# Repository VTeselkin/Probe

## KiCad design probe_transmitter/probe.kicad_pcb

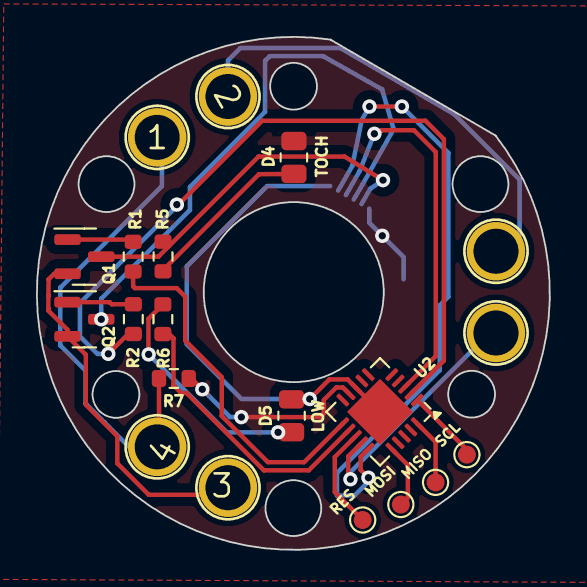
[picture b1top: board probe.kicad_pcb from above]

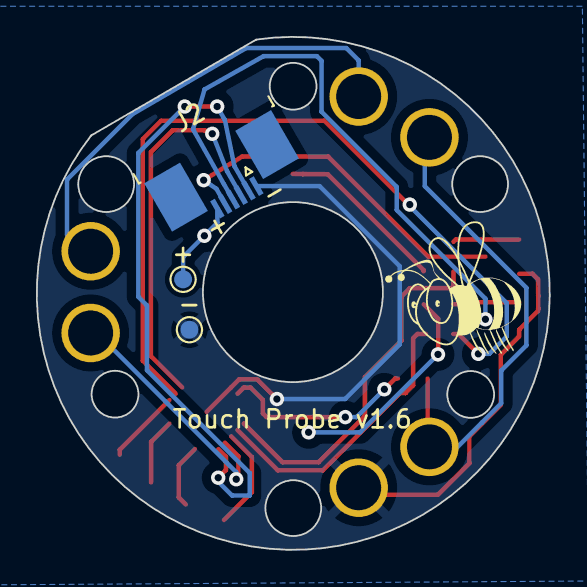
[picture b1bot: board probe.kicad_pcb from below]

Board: 2 copper layers, 28.5 x 28.5 mm, 22 parts (4 on the bottom side), 18 nets.

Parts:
1, 2, 3, 4: (no value)
 : Touch Probe v1.6; LOGO
+: PB0; TestPoint_Pad_D1.0mm
-: PB0; TestPoint_Pad_D1.0mm
D4, D5: LED; R_0805_2012Metric
J2: Conn_01x06; TE_0-1734839-6_1x06-1MP_P0.5mm_Horizontal
MISO: PB1; TestPoint_Pad_D1.0mm
MOSI: PB0; TestPoint_Pad_D1.0mm
Q1, Q2: PMST2222; SOT-23
R1: R1K; R_0603_1608Metric
R2: R1k; R_0603_1608Metric
R5, R6: R39; R_0603_1608Metric
R7: R10M; R_0603_1608Metric
RES: PB5; TestPoint_Pad_D1.0mm
SCL: PB2; TestPoint_Pad_D1.0mm
U2: ATtiny84-20M; QFN-20-1EP_4x4mm_P0.5mm_EP2.6x2.6mm

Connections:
+3.3V: +.1, D4.2 (A), J2.6, R7.2, U2.9 (VCC)
/PAD1: 1.1, 2.1, 4.1, R7.1, U2.14 (PB2)
GND: 3.1, -.1, D5.1 (K), J2.1, Q1.2 (E), Q2.2 (E), U2.8 (GND), U2.21 (GND)
unnamed: D4.1 (K), R5.2
unnamed: D5.2 (A), R6.2
unnamed: J2.2, U2.15 (PA7)
unnamed: J2.3, U2.3 (PA2)
unnamed: J2.4, Q2.3 (C)
unnamed: J2.5, Q1.3 (C), R5.1
unnamed: Q1.1 (B), R1.2
unnamed: Q2.1 (B), R2.2
unnamed: R2.1, U2.2 (PA3)
unnamed: SCL.1, U2.1 (PA4)
unnamed: MISO.1, U2.20 (PA5)
unnamed: MOSI.1, U2.16 (PA6)
unnamed: R1.1, U2.11 (XTAL1/PB0)
unnamed: R6.1, U2.12 (XTAL2/PB1)
unnamed: RES.1, U2.13 (~RESET/PB3)

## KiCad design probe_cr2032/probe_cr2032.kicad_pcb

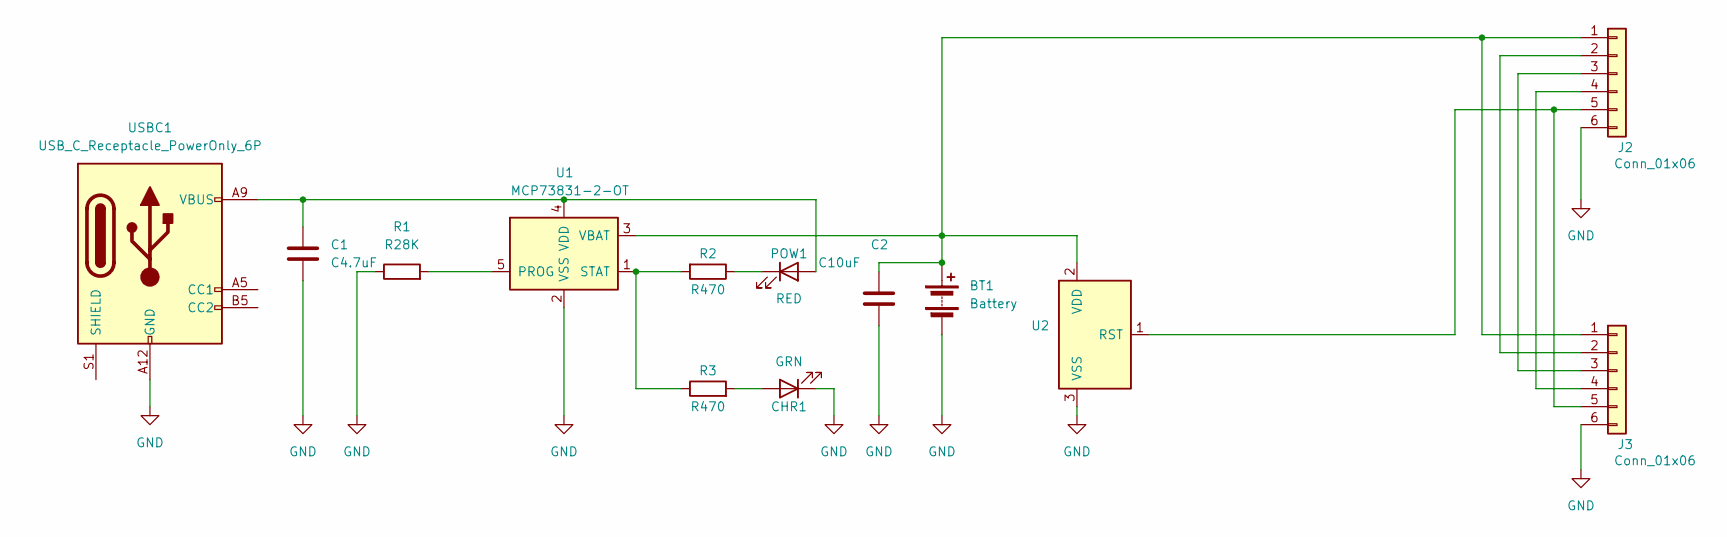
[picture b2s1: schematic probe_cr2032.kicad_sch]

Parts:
BT1: Battery; BatteryHolder_MPD_BC2003_1x2032
C1: C4.7uF; R_0603_1608Metric
C2: C10uF; R_0603_1608Metric
CHR1: GRN; LED_0805_2012Metric
J2, J3: Conn_01x06; TE_0-1734839-6_1x06-1MP_P0.5mm_Horizontal
POW1: RED; LED_0805_2012Metric
R1: R28K; R_0603_1608Metric
R2, R3: R470; R_0603_1608Metric
U1: MCP73831-2-OT; SOT-23-5
U2: MCP101-300D; SOT-23
USBC1: USB_C_Receptacle_PowerOnly_6P; USB_C_Receptacle_GCT_USB4135-GF-A_6P_TopMnt_Horizontal

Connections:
GND: BT1.2 (-), C1.2, C2.2, CHR1.1 (K), J2.6, J3.6, R1.1, U1.2 (VSS), U2.3 (VSS), USBC1.A12 (GND), USBC1.B12 (GND)
unnamed: BT1.1 (+), C2.1, J2.1, J3.1, U1.3 (VBAT), U2.2 (VDD)
unnamed: CHR1.2 (A), R3.2
unnamed: J2.2, J3.2
unnamed: J2.3, J3.3
unnamed: J2.4, J3.4
unnamed: J2.5, J3.5, U2.1 (RST)
unnamed: C1.1, POW1.2 (A), U1.4 (VDD), USBC1.A9 (VBUS), USBC1.B9 (VBUS)
unnamed: POW1.1 (K), R2.1
unnamed: R1.2, U1.5 (PROG)
unnamed: R2.2, R3.1, U1.1 (STAT)

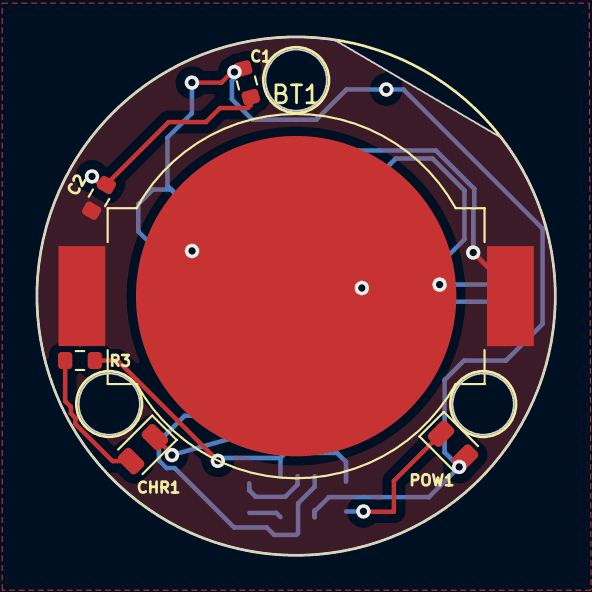
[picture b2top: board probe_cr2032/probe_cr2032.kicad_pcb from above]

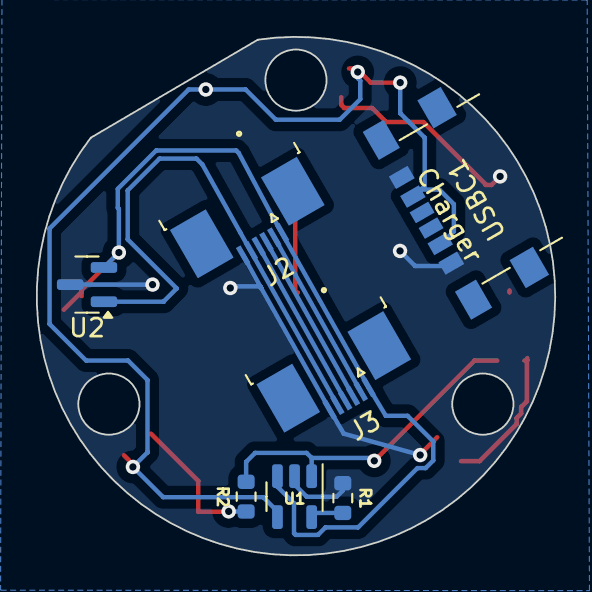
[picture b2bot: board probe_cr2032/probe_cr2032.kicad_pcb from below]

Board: 2 copper layers, 28.8 x 28.8 mm, 13 parts (7 on the bottom side), 11 nets.

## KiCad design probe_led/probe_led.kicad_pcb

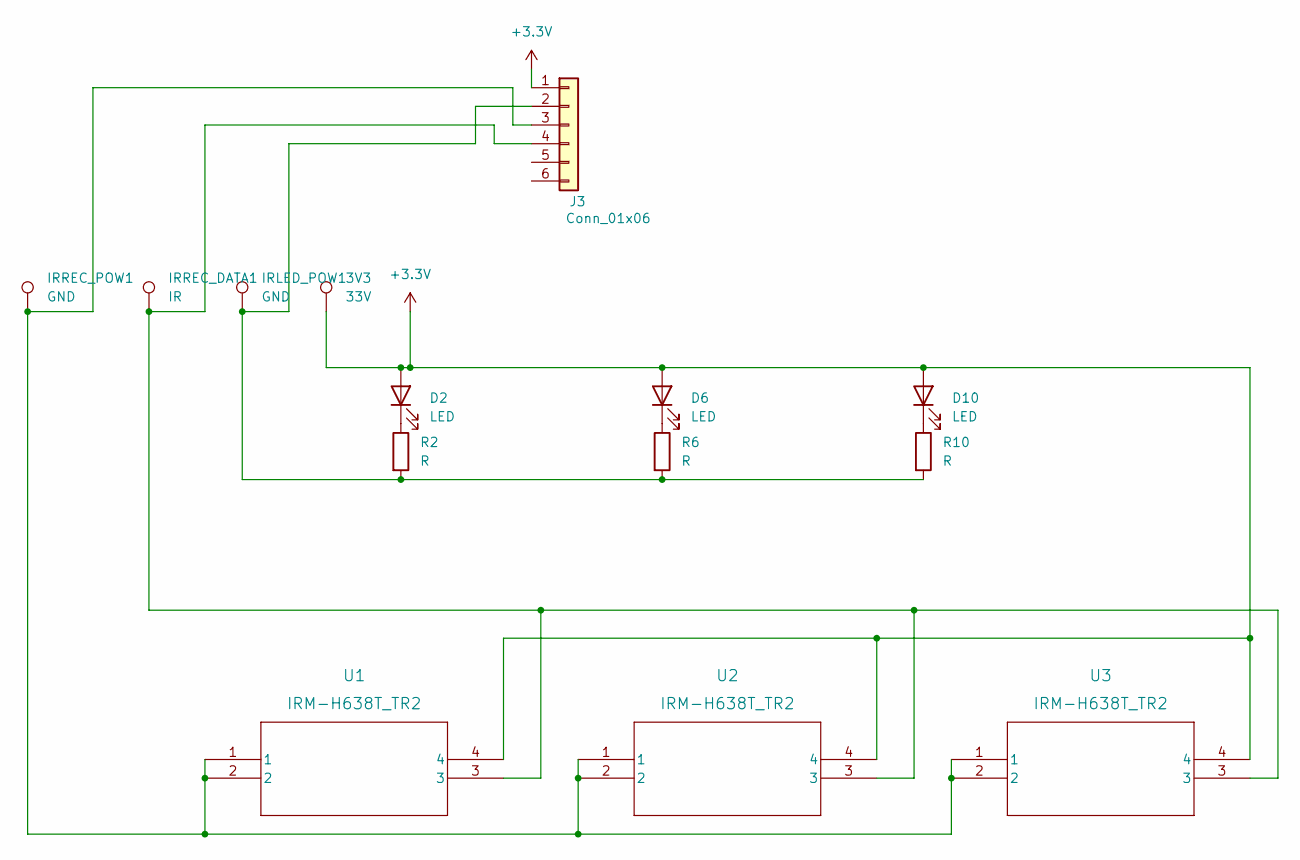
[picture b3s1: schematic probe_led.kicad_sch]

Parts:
3V3: 33V; TestPoint_Pad_D1.0mm
D2, D6, D10: LED; LED_1206_3216Metric_Pad1.42x1.75mm_HandSolder
IRLED_POW1: GND; TestPoint_Pad_D1.0mm
IRREC_DATA1: IR; TestPoint_Pad_D1.0mm
IRREC_POW1: GND; TestPoint_Pad_D1.0mm
J3: Conn_01x06; FPC_4pin_0.5mm_fingers
R2, R6, R10: R; R_0603_1608Metric_Pad0.98x0.95mm_HandSolder
U1, U2, U3: IRM-H638T_TR2; IRM-H638T&slash_TR2_EVE-L

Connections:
+3.3V: 3V3.1, D2.2 (A), D6.2 (A), D10.2 (A), J3.1, U1.4, U2.4, U3.4
unnamed: D2.1 (K), R2.1
unnamed: D6.1 (K), R6.1
unnamed: D10.1 (K), R10.1
unnamed: IRLED_POW1.1, J3.2, R2.2, R6.2, R10.2
unnamed: IRREC_POW1.1, J3.3, U1.1, U1.2, U2.1, U2.2, U3.1, U3.2
unnamed: IRREC_DATA1.1, J3.4, U1.3, U2.3, U3.3

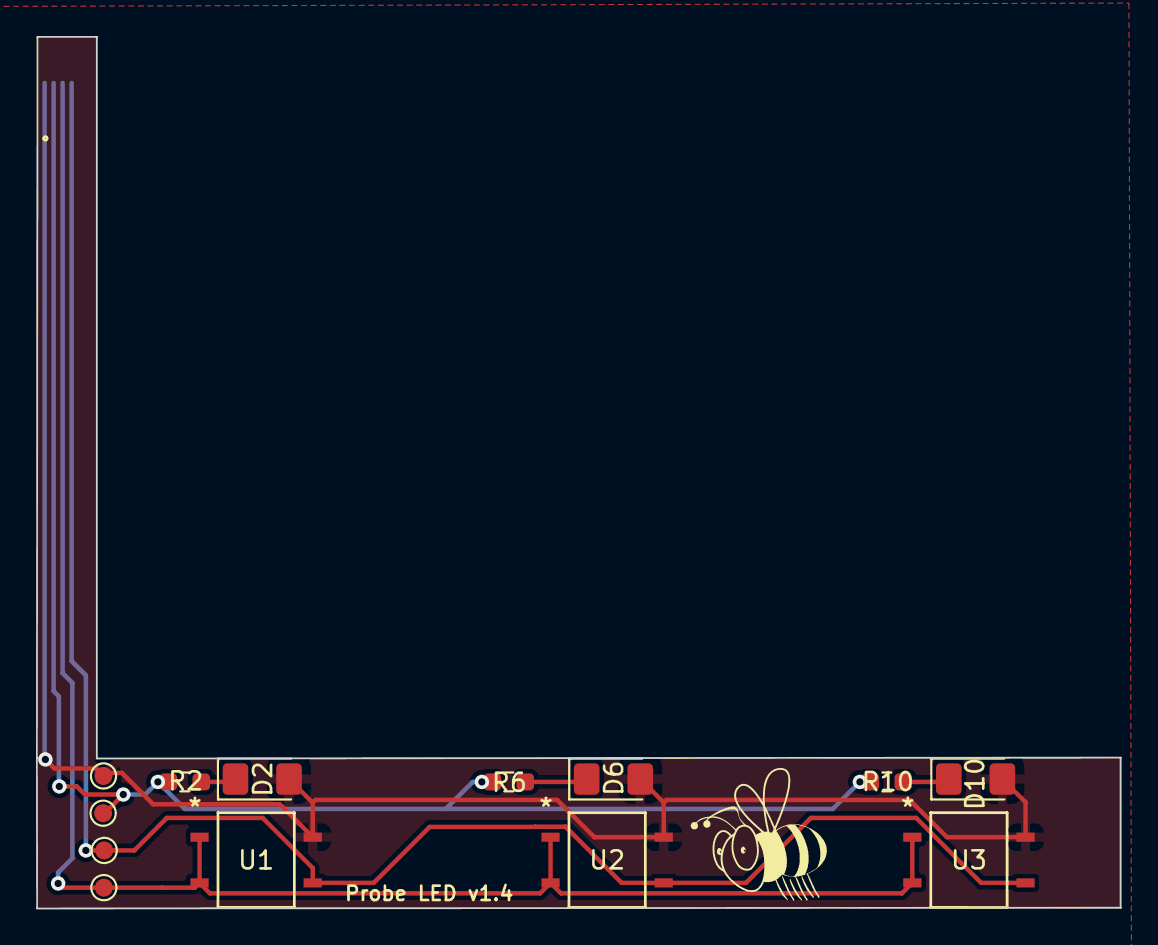
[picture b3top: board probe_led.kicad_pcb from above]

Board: 2 copper layers, 60.2 x 48.4 mm, 15 parts (1 on the bottom side), 7 nets.

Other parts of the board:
 : Probe LED v1.4; LOGO

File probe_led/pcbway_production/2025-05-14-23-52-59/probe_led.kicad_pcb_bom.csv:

Designator,Quantity,Value,Footprint,Package,MPN,DNP,Mount_Type,Description
3V3,1,33V,TestPoint_Pad_D1.0mm,,,,tht,
"D10, D2, D6",3,LED,LED_1206_3216Metric_Pad1.42x1.75mm_HandSolder,,,,smt,
"IRLED_POW1, IRREC_POW1",2,GND,TestPoint_Pad_D1.0mm,,,,tht,
IRREC_DATA1,1,IR,TestPoint_Pad_D1.0mm,,,,tht,
J3,1,Conn_01x06,FPC_4pin_0.5mm_fingers,,,,smt,"Generic connector, single row, 01x06, script generated (kicad-library-utils/schlib/autogen/connector/)"
"R10, R2, R6",3,R,R_0603_1608Metric_Pad0.98x0.95mm_HandSolder,,,,smt,
"U1, U2, U3",3,IRM-H638T_TR2,IRM-H638T&slash_TR2_EVE-L,,,,smt,

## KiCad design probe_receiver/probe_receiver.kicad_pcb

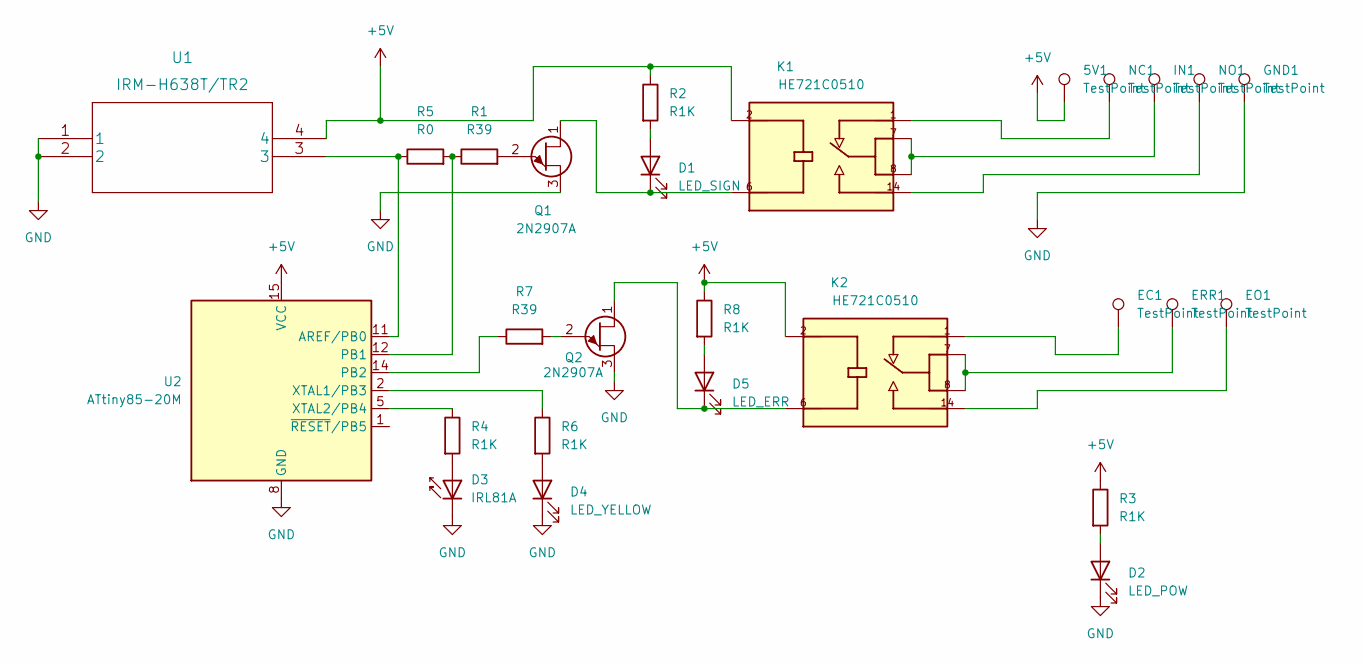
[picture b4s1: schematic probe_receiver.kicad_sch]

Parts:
5V1: TestPoint; TestPoint_Pad_D2.0mm
D1: LED_SIGN; LED_0805_2012Metric
D2: LED_POW; LED_0805_2012Metric
D3: IRL81A; LED_SideEmitter_Rectangular_W4.5mm_H1.6mm
D4: LED_YELLOW; LED_0805_2012Metric
D5: LED_ERR; LED_0805_2012Metric
EC1: TestPoint; TestPoint_Pad_D2.0mm
EO1: TestPoint; TestPoint_Pad_D2.0mm
ERR1: TestPoint; TestPoint_Pad_D2.0mm
GND1: TestPoint; TestPoint_Pad_D2.0mm
IN1: TestPoint; TestPoint_Pad_D2.0mm
K1, K2: HE721C0510; RELAY_HE721C0510; PARTREV BA.12/16/20
NC1: TestPoint; TestPoint_Pad_D2.0mm
NO1: TestPoint; TestPoint_Pad_D2.0mm
Q1, Q2: 2N2907A; TO-18-3
R1, R7: R39; R_0603_1608Metric
R2, R3, R4, R6, R8: R1K; R_0603_1608Metric
R5: R0; R_0201_0603Metric
U1: IRM-H638T/TR2; IRM-H638T&slash_TR2_EVE
U2: ATtiny85-20M; QFN-20-1EP_4x4mm_P0.5mm_EP2.6x2.6mm

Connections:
+5V: 5V1.1, K1.2, K2.2, R2.1, R3.1, R8.1, U1.4, U2.15 (VCC)
GND: D2.1 (K), D3.1 (K), D4.1 (K), GND1.1, Q1.3 (B1), Q2.3 (B1), U1.1, U1.2, U2.8 (GND), U2.21 (GND)
unnamed: D1.1 (K), K1.6, Q1.1 (B2)
unnamed: D1.2 (A), R2.2
unnamed: D2.2 (A), R3.2
unnamed: D4.2 (A), R6.2
unnamed: D5.1 (K), K2.6, Q2.1 (B2)
unnamed: D5.2 (A), R8.2
unnamed: K1.1, NC1.1
unnamed: IN1.1, K1.7, K1.8
unnamed: K1.14, NO1.1
unnamed: EC1.1, K2.1
unnamed: ERR1.1, K2.7, K2.8
unnamed: EO1.1, K2.14
unnamed: Q1.2 (E), R1.2
unnamed: Q2.2 (E), R7.2
unnamed: R1.1, R5.2, U2.12 (PB1)
unnamed: R4.1, U2.5 (XTAL2/PB4)
unnamed: D3.2 (A), R4.2
unnamed: R5.1, U1.3, U2.11 (AREF/PB0)
unnamed: R6.1, U2.2 (XTAL1/PB3)
unnamed: R7.1, U2.14 (PB2)

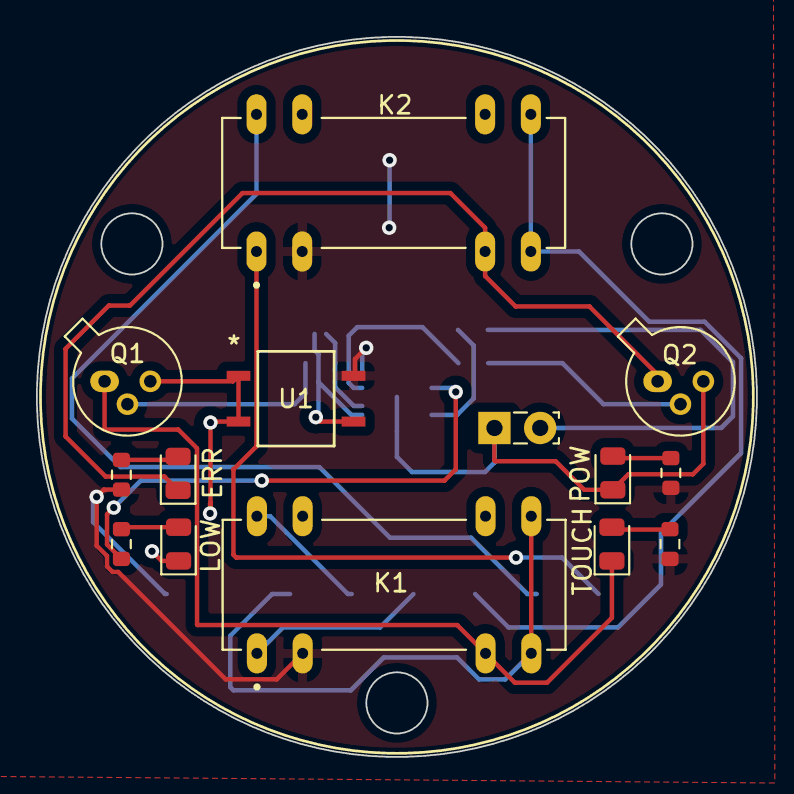
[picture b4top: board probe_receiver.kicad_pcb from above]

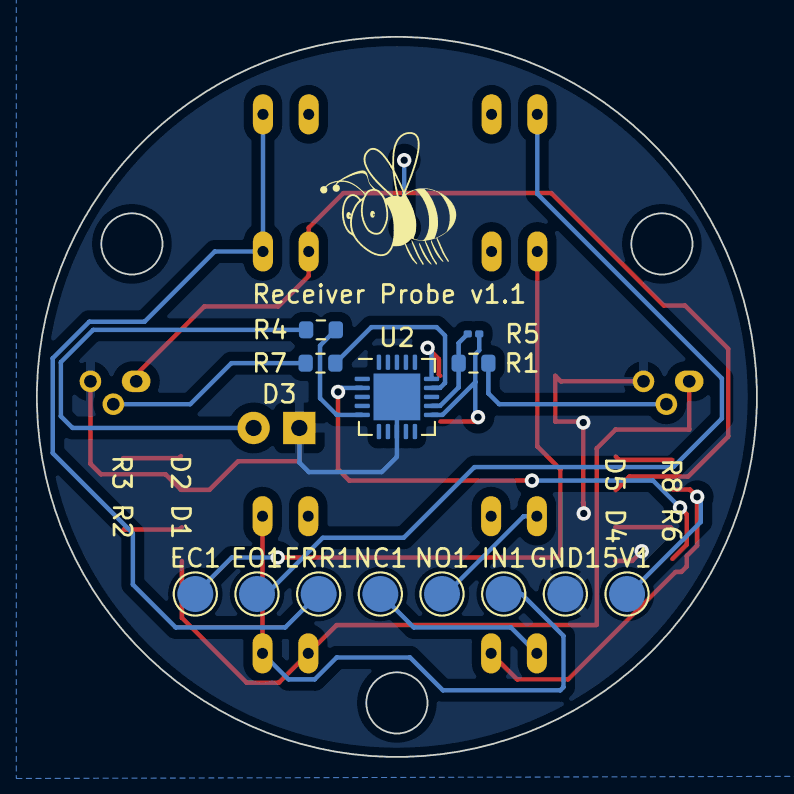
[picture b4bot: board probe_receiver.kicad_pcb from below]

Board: 2 copper layers, 40.0 x 40.0 mm, 28 parts (14 on the bottom side), 22 nets.

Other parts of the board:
 : Receiver Probe v1.1; LOGO

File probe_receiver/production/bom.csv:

Designator,Footprint,Quantity,Value,LCSC Part #
"5V1, EC1, EO1, ERR1, GND1, IN1, NC1, NO1",TestPoint_Pad_D2.0mm,8,TestPoint,
D1,LED_0805_2012Metric,1,LED_SIGN,
D2,LED_0805_2012Metric,1,LED_POW,
D3,LED_SideEmitter_Rectangular_W4.5mm_H1.6mm,1,IRL81A,
D4,LED_0805_2012Metric,1,LED_YELLOW,
D5,LED_0805_2012Metric,1,LED_ERR,
"K1, K2",RELAY_HE721C0510,2,HE721C0510,
"Q1, Q2",TO-18-3,2,2N2907A,
"R1, R7",R_0603_1608Metric,2,R39,
"R2, R3, R4, R6, R8",R_0603_1608Metric,5,R1K,
R5,R_0201_0603Metric,1,R0,
U1,IRM-H638T&slash_TR2_EVE,1,IRM-H638T/TR2,
U2,QFN-20-1EP_4x4mm_P0.5mm_EP2.6x2.6mm,1,ATtiny85-20M,

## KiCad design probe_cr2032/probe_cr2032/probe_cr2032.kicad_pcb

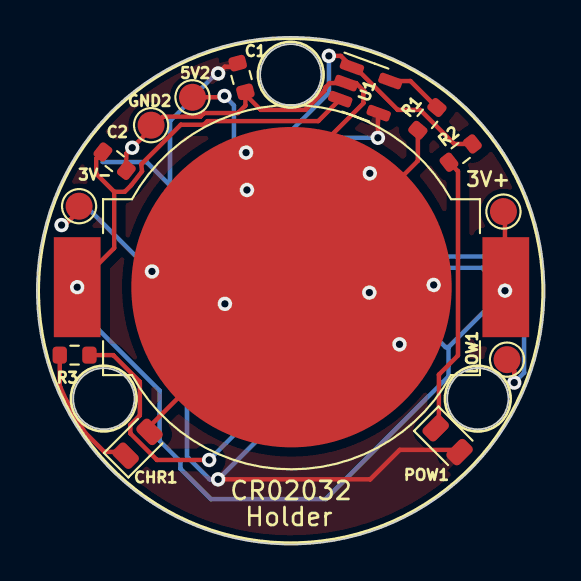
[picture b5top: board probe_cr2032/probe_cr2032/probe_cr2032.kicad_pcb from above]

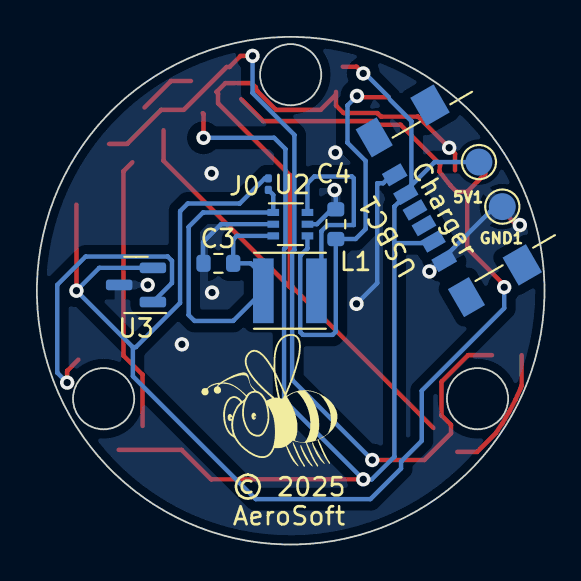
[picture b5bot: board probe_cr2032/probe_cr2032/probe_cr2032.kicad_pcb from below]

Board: 2 copper layers, 28.2 x 28.2 mm, 24 parts (10 on the bottom side), 11 nets.

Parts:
3V+, 3V-, 5V1, 5V2: TestPoint_Pad_D1.5mm
 : iFly; LOGO
C1: C4.7uF; R_0603_1608Metric
C2: C10uF; R_0603_1608Metric
C3: C1uF; R_0603_1608Metric
C4: C22uF; R_0603_1608Metric
CHR1: GRN; LED_0805_2012Metric
CR02032: BAT; BatteryHolder_MPD_BC2003_1x2032
GND1, GND2: TestPoint_Pad_D1.5mm
J0: R0; R_0201_0603Metric
L1: 10UH; L_Vishay_IFSC-1515AH_4x4x1.8mm
LOW1: TestPoint_Pad_D1.5mm
POW1: RED; LED_0805_2012Metric
R1: R28K; R_0603_1608Metric
R2, R3: R470; R_0603_1608Metric
U1: MCP73831-2-OT; SOT-23-5
U2: LTC3525-5; SOT-363_SC-70-6
U3: MCP102-240D; SOT-23
USBC1: USB_C_Receptacle_PowerOnly_6P; USB_C_Receptacle_GCT_USB4135-GF-A_6P_TopMnt_Horizontal

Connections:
+5V: 5V1.1, C1.1, POW1.2 (A), U1.4 (VDD), USBC1.A9 (VBUS), USBC1.B9 (VBUS)
GND: 3V-.1, C1.2, C2.2, C3.2, C4.2, CHR1.2 (A), CR02032.2, GND1.1, GND2.1, R1.1, U1.2 (VSS), U2.2 (GND), U2.5 (GND), U3.3 (VSS), USBC1.A12 (GND), USBC1.B12 (GND)
unnamed: 5V2.1, C4.1, U2.4 (VOUT)
unnamed: C2.1, CR02032.1, J0.1, U1.3 (VBAT), U3.2 (VDD)
unnamed: C3.1, J0.2, L1.1, U2.1 (~SHDN), U2.3 (VIN)
unnamed: CHR1.1 (K), R3.2
unnamed: L1.2, U2.6 (SW)
unnamed: LOW1.1, U3.1 (~RST)
unnamed: POW1.1 (K), R2.1
unnamed: R1.2, U1.5 (PROG)
unnamed: R2.2, R3.1, U1.1 (STAT)

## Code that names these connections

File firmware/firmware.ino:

/*
ATtiny84A QFN20 pin mapping (AttinyCore - Clockwise, QFN-20):

Arduino | Port | Phys.Pin | Comment
----------------------------------------
   0    |  PB0 |  11      | Digital pin 0
   1    |  PB1 |  12      | Digital pin 1
   2    |  PB2 |  14      | Digital pin 2
   3    |  PB3 |  13      | Digital pin 3 (RESET, если не отключён)
   4    |  PA0 |   5      | Digital pin 4 (AREF / Analog In)
   5    |  PA1 |   4      | Digital pin 5
   6    |  PA2 |   3      | Digital pin 6
   7    |  PA3 |   2      | Digital pin 7
   8    |  PA4 |   1      | Digital pin 8
   9    |  PA5 |  20      | Digital pin 9 (PWM)
  10    |  PA6 |  16      | Digital pin 10 (PWM)
  11    |  PA7 |  15      | Digital pin 11 (PWM)

Additional pins (QFN-20 only, **manual access via PORTB**):

   -    |  PB4 |  15      | Manual use only (no Arduino pin)
   -    |  PB5 |  16      | Manual use only (no Arduino pin)
   -    |  PB6 |  17      | Manual use only (no Arduino pin)
   -    |  PB7 |  18      | Manual use only (no Arduino pin)

   QFN-20 Top View (Clockwise Mapping)

    +----+----+
  1 | PA4 | PA3 | 2
 20 | PA5 | PA2 | 3
 19 | NC  | PA1 | 4
 18 | NC  | PA0 | 5
 17 | NC  | NC  | 6
 16 | PA6 | GND | 7
 15 | PA7 | VCC | 8
 14 | PB2 | PB0 | 9
 13 | PB3 | PB1 | 12
    +----+----+
*/

#include <IRremote.h>
#include <avr/sleep.h>
#include <avr/interrupt.h>
#include <avr/power.h>

#define IR_FREQ_KHZ 38

// Пины для ATtiny84 QFN-20 (Clockwise Mapping, AttinyCore)

#define TOUCH_PIN 8  // PB2 - Кнопка (физический пин 14)

#define LOW_POW_LED_PIN 9  // PB1 - Индикатор low power (физический пин 12)
#define LOW_POW_PIN 7      // PA7 - Вход низкого напряжения (физический пин 15)

#define IR_RECEIVER_PIN 3  // PA2 - IR-приёмник (физический пин 3)
#define IR_SEND_PIN 10     // PB0 - IR светодиоды (физический пин 4)
#define IRREC_POW 2        // PA3 - IR-приёмник питание (физический пин 2)

// Команды
#define CMD_REQUEST_STATUS 0xA0
#define CMD_RESPONSE_STATUS 0xA1

IRrecv irrecv(IR_RECEIVER_PIN);
IRsend irsend;

decode_results results;

const int debounceDelay = 1;
const int minXmtLoops = 2000;
const int minLoopTime = 1;

volatile bool isTouchReleased = false;
volatile bool lastTouchState = false;

void setup() {
  pinMode(TOUCH_PIN, INPUT_PULLUP);
  pinMode(IR_SEND_PIN, OUTPUT);
  pinMode(LOW_POW_LED_PIN, OUTPUT);
  pinMode(LOW_POW_PIN, INPUT);
  pinMode(IR_RECEIVER_PIN, INPUT_PULLUP);

  irrecv.enableIRIn();
  irsend.enableIROut(IR_FREQ_KHZ);

  digitalWrite(IR_SEND_PIN, LOW);
  digitalWrite(LOW_POW_LED_PIN, LOW);

  // Начальное состояние кнопки
  lastTouchState = digitalRead(TOUCH_PIN);
  if (lastTouchState == HIGH) {
    isTouchReleased = true;  // Кнопка уже отжата на старте — сразу включаем светодиод
  }
  byte count = 3;
  if (lastTouchState) count = 1;
  for (int i = 0; i < count; i++) {
    digitalWrite(LOW_POW_LED_PIN, HIGH);
    delay(50);
    digitalWrite(LOW_POW_LED_PIN, LOW);
    delay(50);
  }

  // Настройка Pin Change Interrupt на PB (где находится TOUCH_PIN)
  GIMSK |= _BV(PCIE1);
  PCMSK1 |= _BV(PCINT10);  // PB2 - PCINT10

  sei();
}

void sleep() {
  power_all_disable();
  PRR |= _BV(PRTIM0) | _BV(PRTIM1) | _BV(PRUSI);

  set_sleep_mode(SLEEP_MODE_PWR_DOWN);
  sleep_enable();
  sei();
  sleep_cpu();

  // После пробуждения
  sleep_disable();
  power_all_enable();
  PRR &= ~(_BV(PRTIM0) | _BV(PRTIM1) | _BV(PRUSI));
}

// Прерывание по изменению на PB (включая PB2 - TOUCH_PIN)
ISR(PCINT1_vect) {
  bool currentState = digitalRead(TOUCH_PIN);
  if (currentState == HIGH && lastTouchState == LOW) {
    isTouchReleased = true;  // Только отжатие
  }
  lastTouchState = currentState;
}

bool isLowPower() {
  return digitalRead(LOW_POW_PIN) == LOW;
}

void handleTouch() {
  if (isTouchReleased) {
    isTouchReleased = false;
    delay(debounceDelay);

    while (digitalRead(TOUCH_PIN) == HIGH) {
      digitalWrite(IR_SEND_PIN, HIGH);
      delayMicroseconds(12);
      digitalWrite(IR_SEND_PIN, LOW);
      delayMicroseconds(12);

      if (isLowPower() && digitalRead(LOW_POW_LED_PIN) == LOW) {
        digitalWrite(LOW_POW_LED_PIN, HIGH);
      }
    }
  }
}

void loop() {
  handleTouch();
  digitalWrite(LOW_POW_LED_PIN, LOW);
  digitalWrite(IR_SEND_PIN, LOW);
  sleep();
}

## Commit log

2025-01-10 -add last changes
2025-01-10 -remove files
2025-01-11 -add firmware
2025-01-13 - add fix for PCB v1.1 (fix resistor place 1608)
2025-01-26 -add probe led
2025-01-26 - update probe cr_2032
2025-01-26 - update probe reciver to v1.1
2025-01-26 - update probe transmitter
2025-01-26 - add irremote library
2025-02-02 - v .1.1 in prode
2025-02-17 - add led pcb
2025-03-02 - add lasr fix
2025-03-03 - last fix
2025-03-03 - fix firmware
2025-03-03 -add last fix
2025-03-20 - add new power version
2025-05-01 -update version Kicad
2025-05-01 -add new size led
2025-05-08 -add new version for transmitter
2025-05-09 - add new probe_cr_2032
2025-05-13 -prepare for production
2025-05-15 - set to production
2025-06-29 -add last fix for attinty84
2025-07-08 -add firmware for attiny84a
2025-07-13 -add fix connector
2025-07-14 - fix mapping pins
2025-07-14 -add last fix for firmware
2025-07-19 -add to production
2025-08-04 -change hole ball 3.25/2.5
2025-08-05 -add 4.54mm ball distance

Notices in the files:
probe_cr2032/probe_cr2032/probe_cr2032.kicad_pcb:
© 2025
